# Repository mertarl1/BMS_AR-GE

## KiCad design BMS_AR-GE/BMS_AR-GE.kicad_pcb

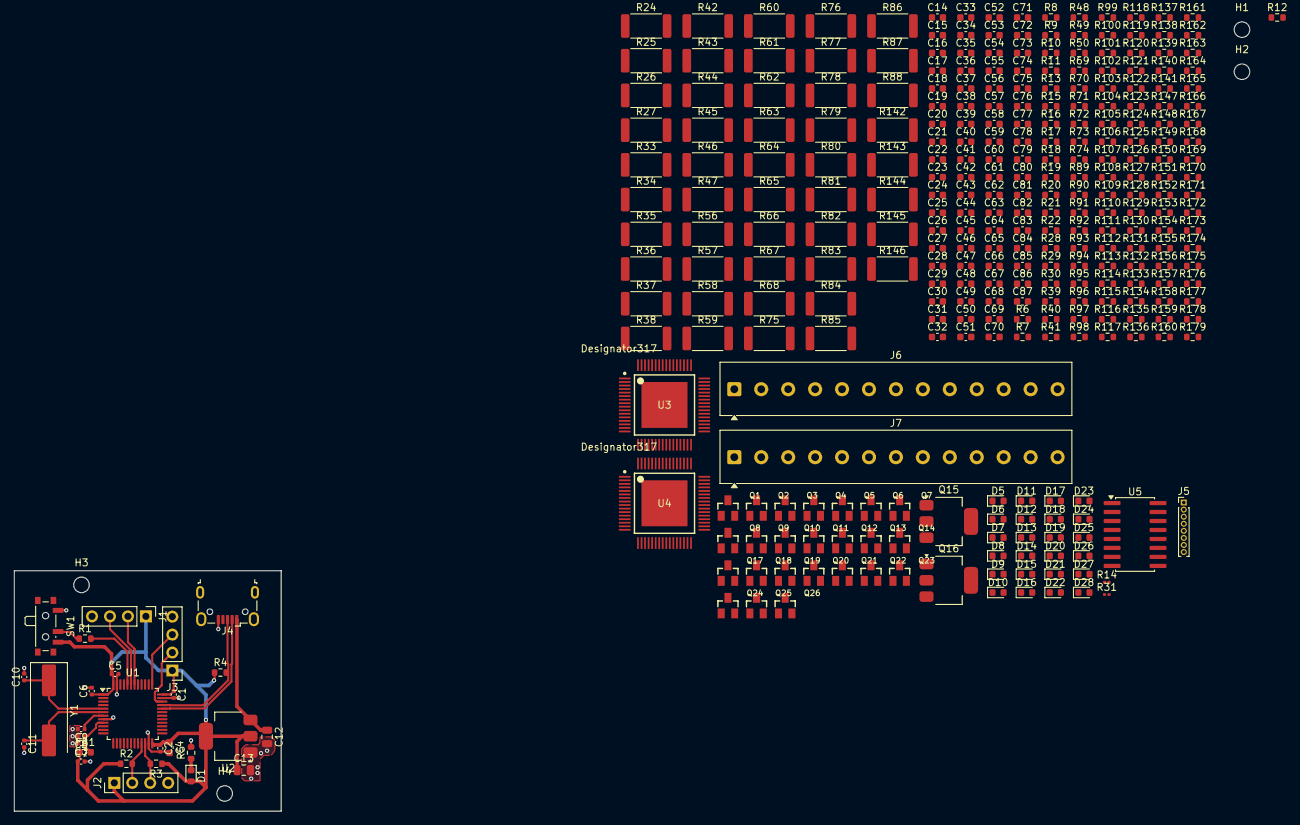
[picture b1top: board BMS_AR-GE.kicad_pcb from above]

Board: 2 copper layers, 37.8 x 34.0 mm, 329 parts (0 on the bottom side), 231 nets.

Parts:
C1, C2, C5, C6, C9: 100n; C_0402_1005Metric
C3: 10n; C_0402_1005Metric
C4: 10u; C_0603_1608Metric
C7, C8: 1u; C_0402_1005Metric
C10, C11: 10p; C_0402_1005Metric
C12, C13: 22u; C_0805_2012Metric
C14, C18, C48, C51, C54, C59: 0.1u; C_0603_1608Metric
C15, C55: 0.22u; C_0603_1608Metric
C16, C56: 10n; C_0603_1608Metric
C17, C21, C22, C49, C50, C53, C57, C61: 1u; C_0603_1608Metric
C19, C60: 2.2u; C_0603_1608Metric
C20, C58: 4.7u; C_0603_1608Metric
C23, C24, C25, C26, C27, C28, C29, C30, C31, C32, C33, C34, C35, C36, C37, C38, C39, C40, C41, C42, C43, C44, C45, C46, C47, C52, C62, C63, C64, C65, C66, C67, C68, C69, C70, C71, C72, C73, C74, C75, C76, C77, C78, C79, C80, C81, C82, C83, C84, C85, C86, C87: 0.47u; C_0603_1608Metric
D1, D5, D6, D7, D8, D9, D10, D11, D12, D13, D14, D15, D16, D17, D18, D19, D20, D21, D22, D23, D24, D25, D26, D27, D28: LED; LED_0603_1608Metric
FB1: 120R; L_0603_1608Metric
H1, H2, H3, H4: MountingHole; MountingHole_2.2mm_M2
J1, J2, J3: Conn_01x04_Pin; PinHeader_1x04_P2.54mm_Vertical
J4: USB_B_Micro; USB_Micro-B_Wuerth_629105150521
J5: Conn_01x08_Pin; PinHeader_1x08_P1.00mm_Vertical
J6, J7: Conn_01x13_Pin; TerminalBlock_Phoenix_MKDS-1-13-3.81_1x13_P3.81mm_Horizontal
Q1, Q2, Q3, Q4, Q5, Q6, Q7, Q8, Q9, Q10, Q11, Q12, Q13, Q14, Q17, Q18, Q19, Q20, Q21, Q22, Q23, Q24, Q25, Q26: NDS332P; SSOT-3
Q15, Q16: BCP56; SOT-223
R1: 10k; R_0603_1608Metric
R2, R3, R4, R5: 1k5; R_0603_1608Metric
R6, R17: 200; R_0603_1608Metric
R7, R21, R93, R94, R95, R96, R97, R98, R99, R100, R101, R102, R103, R104, R105, R106, R107, R109, R111, R113, R115, R117, R119, R121, R123, R125, R127, R128, R129, R130, R131, R132, R133, R134, R135, R136, R137, R138, R139, R140, R141, R167, R168, R169, R170, R171, R172, R173, R174, R175, R176, R177, R178, R179: 100; R_0603_1608Metric
R8, R20: 30; R_0603_1608Metric
R9, R10, R29, R30: 0; R_0603_1608Metric
R11, R12, R28: 2.2K; R_0603_1608Metric
R13, R22, R39, R40, R41, R48, R49, R50, R69, R70, R71, R72, R73, R74, R89, R90, R147, R148, R149, R150, R151, R152, R153, R154: 330; R_0603_1608Metric
R14, R31: 1K; R_0201_0603Metric
R15, R16, R18, R19: 10K; R_0603_1608Metric
R24, R25, R26, R27, R33, R34, R35, R36, R37, R38, R42, R43, R44, R45, R46, R47, R56, R57, R58, R59, R60, R61, R62, R63, R64, R65, R66, R67, R68, R75, R76, R77, R78, R79, R80, R81, R82, R83, R84, R85, R86, R87, R88, R142, R143, R144, R145, R146: 39; R_2512_6332Metric
R91, R92, R108, R110, R112, R114, R116, R118, R120, R122, R124, R126, R155, R156, R157, R158, R159, R160, R161, R162, R163, R164, R165, R166: 1k; R_0603_1608Metric
SW1: SW_SPDT; SW_SPDT_PCM12
U1: STM32F103C8Tx; LQFP-48_7x7mm_P0.5mm
U2: AMS1117-3.3; SOT-223-3_TabPin2
U3: BQ79612-Q1; PAP0064F-IPC_B
U4: BQ79652-Q1; PAP0064F-IPC_B
U5: ISO6731; SOIC-16W_5.3x10.2mm_P1.27mm
Y1: 8MHz; Crystal_SMD_HC49-SD

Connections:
+3.3VA: C3.1, C8.1, FB1.2, U1.9 (VDDA)
/BALANCING/BA15+: D25.1 (K), Q24.2, R78.2, R84.2, R138.2, R164.2
/BALANCING/BAT1+: D15.1 (K), J6.2, Q1.2, R85.2, R87.2, R92.2, R95.2
/BALANCING/BAT1-: D16.1 (K), J6.1, R86.2, R88.2, R94.2, R128.2
/BALANCING/BAT2+: D14.1 (K), J6.3, Q2.2, R64.2, R68.2, R91.2, R97.2
/BALANCING/BAT3+: D13.1 (K), J6.4, Q3.2, R61.2, R67.2, R98.2, R108.2
/BALANCING/BAT4+: D12.1 (K), J6.5, Q4.2, R60.2, R66.2, R99.2, R110.2
/BALANCING/BAT5+: D11.1 (K), J6.6, Q5.2, R59.2, R65.2, R100.2, R112.2
/BALANCING/BAT6+: D10.1 (K), J6.7, Q6.2, R57.2, R63.2, R101.2, R114.2
/BALANCING/BAT7+: D9.1 (K), J6.8, Q7.2, R56.2, R62.2, R102.2, R116.2
/BALANCING/BAT8+: D8.1 (K), J6.9, Q8.2, R35.2, R38.2, R103.2, R118.2
/BALANCING/BAT9+: D7.1 (K), J6.10, Q9.2, R34.2, R37.2, R104.2, R120.2
/BALANCING/BAT10+: D6.1 (K), J6.11, Q10.2, R33.2, R36.2, R105.2, R122.2
/BALANCING/BAT11+: D5.1 (K), J6.12, Q11.2, R24.2, R25.2, R106.2, R124.2
/BALANCING/BAT12+: D28.1 (K), J6.13, J7.1, Q12.2, R6.1, R8.1, R107.2, R126.2, R140.2, R143.2, R146.2, R178.2, U4.2 (CB16), U4.3 (VC16), U4.4 (CB15), U4.5 (VC15), U4.6 (CB14), U4.7 (VC14), U4.8 (CB13), U4.9 (VC13)
/BALANCING/BAT13+: D27.1 (K), J7.2, Q26.2, R141.2, R142.2, R145.2, R166.2
/BALANCING/BAT14+: D26.1 (K), J7.3, Q25.2, R79.2, R139.2, R144.2, R165.2
/BALANCING/BAT16+: D24.1 (K), J7.5, Q23.2, R77.2, R83.2, R137.2, R163.2
/BALANCING/BAT17+: D23.1 (K), J7.6, Q22.2, R76.2, R82.2, R136.2, R162.2
/BALANCING/BAT18+: D22.1 (K), J7.7, Q21.2, R75.2, R81.2, R135.2, R161.2
/BALANCING/BAT19+: D21.1 (K), J7.8, Q20.2, R58.2, R80.2, R134.2, R160.2
/BALANCING/BAT20+: D20.1 (K), J7.9, Q19.2, R44.2, R47.2, R133.2, R159.2
/BALANCING/BAT21+: D19.1 (K), J7.10, Q18.2, R43.2, R46.2, R132.2, R158.2
/BALANCING/BAT22+: D18.1 (K), J7.11, Q17.2, R42.2, R45.2, R131.2, R157.2
/BALANCING/BAT23+: D17.1 (K), J7.12, Q14.2, R26.2, R27.2, R130.2, R156.2
/BALANCING/BAT24+: J7.13, Q13.2, R17.1, R20.1, R129.2, R155.2, U3.2 (CB16), U3.3 (VC16), U3.4 (CB15), U3.5 (VC15), U3.6 (CB14), U3.7 (VC14), U3.8 (CB13), U3.9 (VC13)
/BALANCING/CB0: R128.1, U4.34 (CB0)
/BALANCING/CB1: C46.2, C47.1, R93.1, U4.32 (CB1)
/BALANCING/CB2: R96.1, U4.30 (CB2)
/BALANCING/CB3: R109.1, U4.28 (CB3)
/BALANCING/CB4: R111.1, U4.26 (CB4)
/BALANCING/CB5: R113.1, U4.24 (CB5)
/BALANCING/CB6: R115.1, U4.22 (CB6)
/BALANCING/CB7: R117.1, U4.20 (CB7)
/BALANCING/CB8: R119.1, U4.18 (CB8)
/BALANCING/CB9: R121.1, U4.16 (CB9)
/BALANCING/CB10: R123.1, U4.14 (CB10)
/BALANCING/CB11: C36.2, C37.1, R125.1, U4.12 (CB11)
/BALANCING/CB12: C36.1, R127.1, R178.1, U3.34 (CB0), U4.10 (CB12)
/BALANCING/CB13: C85.2, C86.1, R179.1, U3.32 (CB1)
/BALANCING/CB14: R177.1, U3.30 (CB2)
/BALANCING/CB15: R176.1, U3.28 (CB3)
/BALANCING/CB16: R175.1, U3.26 (CB4)
/BALANCING/CB17: R174.1, U3.24 (CB5)
/BALANCING/CB18: R173.1, U3.22 (CB6)
/BALANCING/CB19: R172.1, U3.20 (CB7)
/BALANCING/CB20: R171.1, U3.18 (CB8)
/BALANCING/CB21: R170.1, U3.16 (CB9)
/BALANCING/CB22: R169.1, U3.14 (CB10)
/BALANCING/CB23: C75.2, C76.1, R168.1, U3.12 (CB11)
/BALANCING/CB24: C75.1, R167.1, U3.10 (CB12)
/BALANCING/GPIO1: J5.1, R15.1, U4.61 (GPIO1)
/BALANCING/GPIO2: J5.3, R16.1, U4.60 (GPIO2)
/BALANCING/GPIO3: J5.5, R18.1, U4.59 (GPIO3)
/BALANCING/GPIO4: J5.7, R19.1, U4.58 (GPIO4)
/BALANCING/RX: R11.2, U4.52 (RX), U5.5 (OUTC)
/BALANCING/TX: U4.53 (TX), U5.3 (INA)
/BALANCING/VC0: C23.2, C24.1, R94.1, U4.35 (VC0)
/BALANCING/VC1: C23.1, C25.2, R95.1, U4.33 (VC1)
/BALANCING/VC2: C25.1, C26.2, R97.1, U4.31 (VC2)
/BALANCING/VC3: C26.1, C27.2, R98.1, U4.29 (VC3)
/BALANCING/VC4: C27.1, C28.2, R99.1, U4.27 (VC4)
/BALANCING/VC5: C28.1, C29.2, R100.1, U4.25 (VC5)
/BALANCING/VC6: C29.1, C30.2, R101.1, U4.23 (VC6)
/BALANCING/VC7: C30.1, C31.2, R102.1, U4.21 (VC7)
/BALANCING/VC8: C31.1, C32.2, R103.1, U4.19 (VC8)
/BALANCING/VC9: C32.1, C33.2, R104.1, U4.17 (VC9)
/BALANCING/VC10: C33.1, C34.2, R105.1, U4.15 (VC10)
/BALANCING/VC11: C34.1, C35.2, R106.1, U4.13 (VC11)
/BALANCING/VC12: C35.1, C73.2, C74.1, R107.1, R140.1, U3.35 (VC0), U4.11 (VC12)
/BALANCING/VC13: C72.2, C73.1, R141.1, U3.33 (VC1)
/BALANCING/VC14: C71.2, C72.1, R139.1, U3.31 (VC2)
/BALANCING/VC15: C70.2, C71.1, R138.1, U3.29 (VC3)
/BALANCING/VC16: C69.2, C70.1, R137.1, U3.27 (VC4)
/BALANCING/VC17: C68.2, C69.1, R136.1, U3.25 (VC5)
/BALANCING/VC18: C67.2, C68.1, R135.1, U3.23 (VC6)
/BALANCING/VC19: C66.2, C67.1, R134.1, U3.21 (VC7)
/BALANCING/VC20: C65.2, C66.1, R133.1, U3.19 (VC8)
/BALANCING/VC21: C64.2, C65.1, R132.1, U3.17 (VC9)
/BALANCING/VC22: C63.2, C64.1, R131.1, U3.15 (VC10)
/BALANCING/VC23: C62.2, C63.1, R130.1, U3.13 (VC11)
/BALANCING/VC24: C62.1, R129.1, U3.11 (VC12)
/D+: J4.3 (D+), R4.2, U1.33 (PA12)
/D-: J4.2 (D-), U1.32 (PA11)
/I2C2_SCL: J2.2, R2.2, U1.21 (PB10)
/I2C2_SDA: J2.3, R3.2, U1.22 (PB11)
/SWCLK: J3.3, U1.37 (PA14)
/SWDIO: J3.2, U1.34 (PA13)
CVDD: C20.2, R11.1, U4.45 (CVDD)
CVDD1: C58.2, R28.1, U3.45 (CVDD)
DVDD: C19.2, C48.1, C49.1, U4.49 (DVDD), U5.1 (V_{CC1}), U5.7 (EN1)
DVDD1: C60.2, U3.49 (DVDD)
DVSS: C19.1, C48.2, C49.2, U4.50 (DVSS), U5.2 (GND1), U5.8 (GND1)
DVSS1: C60.1, U3.50 (DVSS)
GND: C1.2, C2.2, C3.2, C4.2, C5.2, C6.2, C7.2, C8.2, C9.2, C10.2, C11.2, C12.2, C13.2, C15.1, C16.1, C50.2, C51.2, J1.4, J2.4, J3.4, J4.5 (GND), J5.2, J5.4, J5.6, J5.8, R5.2, R9.1, R10.1, SW1.1 (A), U1.8 (VSSA), U1.23 (VSS), U1.35 (VSS), U1.47 (VSS), U2.1 (GND), U5.9 (GND2), U5.15 (GND2)
GND1: C55.1, C56.1, R29.1, R30.1
GNDA: C17.1, C24.2, C52.2, U4.39 (AVSS)
GNDA1: C57.1, C74.2, C87.2, U3.39 (AVSS)
GNDC: C14.1, C18.1, C20.1, C21.1, U4.46 (CVSS)
GNDC1: C53.1, C54.1, C58.1, C59.1, U3.46 (CVSS)
GNDR: C22.1, U4.36 (REFHM)
GNDR1: C61.1, U3.36 (REFHM)
unnamed: C15.2, Q15.4 (C), R7.2
unnamed: C37.2, C38.1
unnamed: C38.2, C39.1
unnamed: C39.2, C40.1
unnamed: C40.2, C41.1
unnamed: C41.2, C42.1
unnamed: C42.2, C43.1
unnamed: C43.2, C44.1
unnamed: C44.2, C45.1
unnamed: C45.2, C46.1
unnamed: C47.2, C52.1
unnamed: C55.2, Q16.4 (C), R21.2
unnamed: C76.2, C77.1
unnamed: C77.2, C78.1
unnamed: C78.2, C79.1
unnamed: C79.2, C80.1
unnamed: C80.2, C81.1
unnamed: C81.2, C82.1
unnamed: C82.2, C83.1
unnamed: C83.2, C84.1
unnamed: C84.2, C85.1
unnamed: C86.2, C87.1
unnamed: D1.1 (K), R5.1
unnamed: D5.2 (A), R13.1
unnamed: D6.2 (A), R39.1
unnamed: D7.2 (A), R40.1
unnamed: D8.2 (A), R41.1
unnamed: D9.2 (A), R69.1
unnamed: D10.2 (A), R70.1
unnamed: D11.2 (A), R71.1
unnamed: D12.2 (A), R72.1
unnamed: D13.2 (A), R73.1
unnamed: D14.2 (A), R74.1
unnamed: D15.2 (A), R89.1
unnamed: D16.2 (A), R90.1
unnamed: D17.2 (A), R22.1
unnamed: D18.2 (A), R48.1
unnamed: D19.2 (A), R49.1
unnamed: D20.2 (A), R50.1
unnamed: D21.2 (A), R147.1
unnamed: D22.2 (A), R148.1
unnamed: D23.2 (A), R149.1
unnamed: D24.2 (A), R150.1
unnamed: D25.2 (A), R151.1
unnamed: D26.2 (A), R152.1
unnamed: D27.2 (A), R153.1
unnamed: D28.2 (A), R154.1
unnamed: Q1.1, R92.1, R93.2
unnamed: Q1.3, R86.1, R88.1, R90.2
unnamed: Q2.1, R91.1, R96.2
unnamed: Q2.3, R85.1, R87.1, R89.2
unnamed: Q3.1, R108.1, R109.2
unnamed: Q3.3, R64.1, R68.1, R74.2
unnamed: Q4.1, R110.1, R111.2
unnamed: Q4.3, R61.1, R67.1, R73.2
unnamed: Q5.1, R112.1, R113.2
unnamed: Q5.3, R60.1, R66.1, R72.2
unnamed: Q6.1, R114.1, R115.2
unnamed: Q6.3, R59.1, R65.1, R71.2
unnamed: Q7.1, R116.1, R117.2
unnamed: Q7.3, R57.1, R63.1, R70.2
unnamed: Q8.1, R118.1, R119.2
unnamed: Q8.3, R56.1, R62.1, R69.2
unnamed: Q9.1, R120.1, R121.2
unnamed: Q9.3, R35.1, R38.1, R41.2
unnamed: Q10.1, R122.1, R123.2
unnamed: Q10.3, R34.1, R37.1, R40.2
unnamed: Q11.1, R124.1, R125.2
unnamed: Q11.3, R33.1, R36.1, R39.2
unnamed: Q12.1, R126.1, R127.2
unnamed: Q12.3, R13.2, R24.1, R25.1
unnamed: Q13.1, R155.1, R167.2
unnamed: Q13.3, R22.2, R26.1, R27.1
unnamed: Q14.1, R156.1, R168.2
unnamed: Q14.3, R42.1, R45.1, R48.2
unnamed: Q15.1 (B), U4.48 (NPNB)
unnamed: C14.2, Q15.3 (E), U4.47 (LDOIN)
unnamed: Q16.1 (B), U3.48 (NPNB)
unnamed: C54.2, Q16.3 (E), U3.47 (LDOIN)
unnamed: Q17.1, R157.1, R169.2
unnamed: Q17.3, R43.1, R46.1, R49.2
unnamed: Q18.1, R158.1, R170.2
unnamed: Q18.3, R44.1, R47.1, R50.2
unnamed: Q19.1, R159.1, R171.2
unnamed: Q19.3, R58.1, R80.1, R147.2
unnamed: Q20.1, R160.1, R172.2
unnamed: Q20.3, R75.1, R81.1, R148.2
unnamed: Q21.1, R161.1, R173.2
unnamed: Q21.3, R76.1, R82.1, R149.2
unnamed: Q22.1, R162.1, R174.2
unnamed: Q22.3, R77.1, R83.1, R150.2
unnamed: Q23.1, R163.1, R175.2
unnamed: Q23.3, R78.1, R84.1, R151.2
unnamed: Q24.1, R164.1, R176.2
unnamed: Q24.3, R79.1, R144.1, R152.2
unnamed: Q25.1, R165.1, R177.2
unnamed: Q25.3, R142.1, R145.1, R153.2
unnamed: Q26.1, R166.1, R179.2
unnamed: Q26.3, R143.1, R146.1, R154.2
unnamed: R6.2, R7.1
unnamed: R17.2, R21.1
unnamed: R1.1, SW1.2 (B)
unnamed: R1.2, U1.44 (BOOT0)
unnamed: C9.1, U1.7 (NRST)
unnamed: C10.1, U1.5 (PD0), Y1.1
unnamed: C11.1, U1.6 (PD1), Y1.2
unnamed: C57.2, U3.38 (AVDD)
unnamed: C56.2, R20.2, U3.1 (BAT)
unnamed: R30.2, U3.63 (BBN)
unnamed: R29.2, U3.64 (BBP)
unnamed: R31.2, U3.42 (COMHN)
unnamed: R31.1, U3.43 (COMHP)
unnamed: C59.2, U3.44 (NEG5V)
unnamed: C61.2, U3.37 (REFHP)
unnamed: R28.2, U3.52 (RX)
unnamed: C53.2, U3.51 (TSREF)
unnamed: C17.2, U4.38 (AVDD)
unnamed: C16.2, R8.2, U4.1 (BAT)
unnamed: R14.2, U4.41 (COMLN)
unnamed: R14.1, U4.40 (COMLP)
unnamed: C18.2, U4.44 (NEG5V)
unnamed: C22.2, U4.37 (REFHP)
unnamed: R10.2, U4.63 (SRN)
unnamed: R9.2, U4.64 (SRP)
unnamed: C21.2, R15.2, R16.2, R18.2, R19.2, U4.51 (TSREF)
STM_RX: J1.3, R12.1, U1.43 (PB7), U5.14 (OUTA)
STM_TX: J1.2, U1.42 (PB6), U5.12 (INC)
VBUS: C12.1, J4.1 (VBUS), U2.3 (VI)
VDD_3V3: C1.1, C2.1, C4.1, C5.1, C6.1, C7.1, C13.1, C50.1, C51.1, D1.2 (A), FB1.1, J1.1, J2.1, J3.1, R2.1, R3.1, R4.1, R12.2, SW1.3 (C), U1.1 (VBAT), U1.24 (VDD), U1.36 (VDD), U1.48 (VDD), U2.2 (VO), U5.10 (EN2), U5.16 (V_{CC2})
